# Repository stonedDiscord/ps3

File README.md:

# Playstation 3 schematics and board layout

This is a WIP KiCAD project for a custom PS3 motherboard.

I don't know if it's realistic but just maybe it's possible to use a newer CELL and RSX together with the PS2 EE/GS chips, since after all it's just simple PCI between them.

Shoutout to the PS3 dev wiki, it's been incredible helpful so far:
https://www.psdevwiki.com/ps3/Motherboard_Components

If you have high quality stripped board scans, I would appreciate a PR or an E-Mail with them.

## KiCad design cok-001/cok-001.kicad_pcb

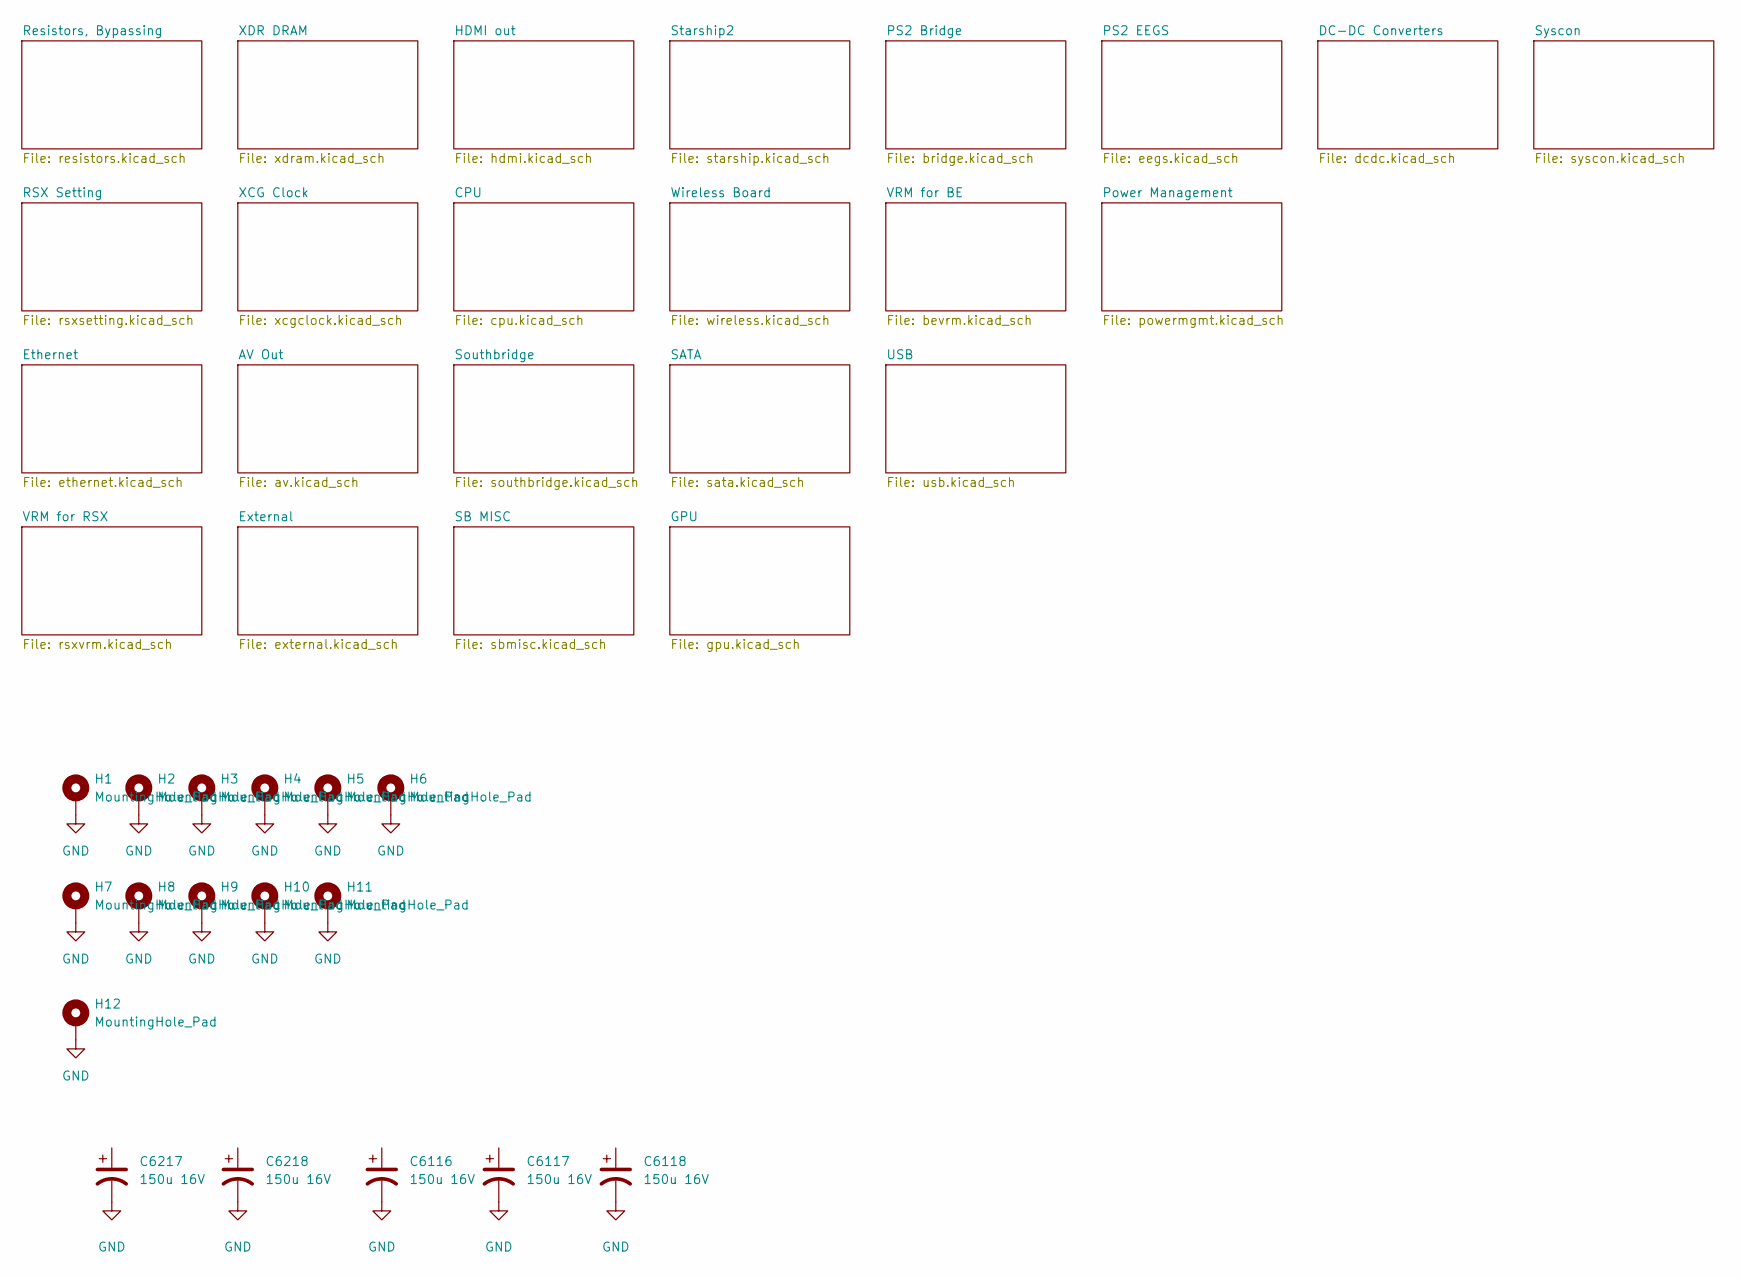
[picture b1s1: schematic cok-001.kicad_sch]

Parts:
C6116, C6117, C6118, C6217, C6218: 150u 16V; CP_Elec_8x6.9
H1, H2, H3, H4, H5, H6, H7, H8, H9, H10, H11: MountingHole_Pad; MountingHole_4.3mm_M4_Pad_Via
H12: MountingHole_Pad; MountingHole_4.3x6.2mm_M4_Pad_Via

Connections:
GND: C6116.2, C6117.2, C6118.2, C6217.2, C6218.2, H1.1 (1_1), H2.1 (1_1), H3.1 (1_1), H4.1 (1_1), H5.1 (1_1), H6.1 (1_1), H7.1 (1_1), H8.1 (1_1), H9.1 (1_1), H10.1 (1_1), H11.1 (1_1), H12.1 (1_1); also elsewhere on the board

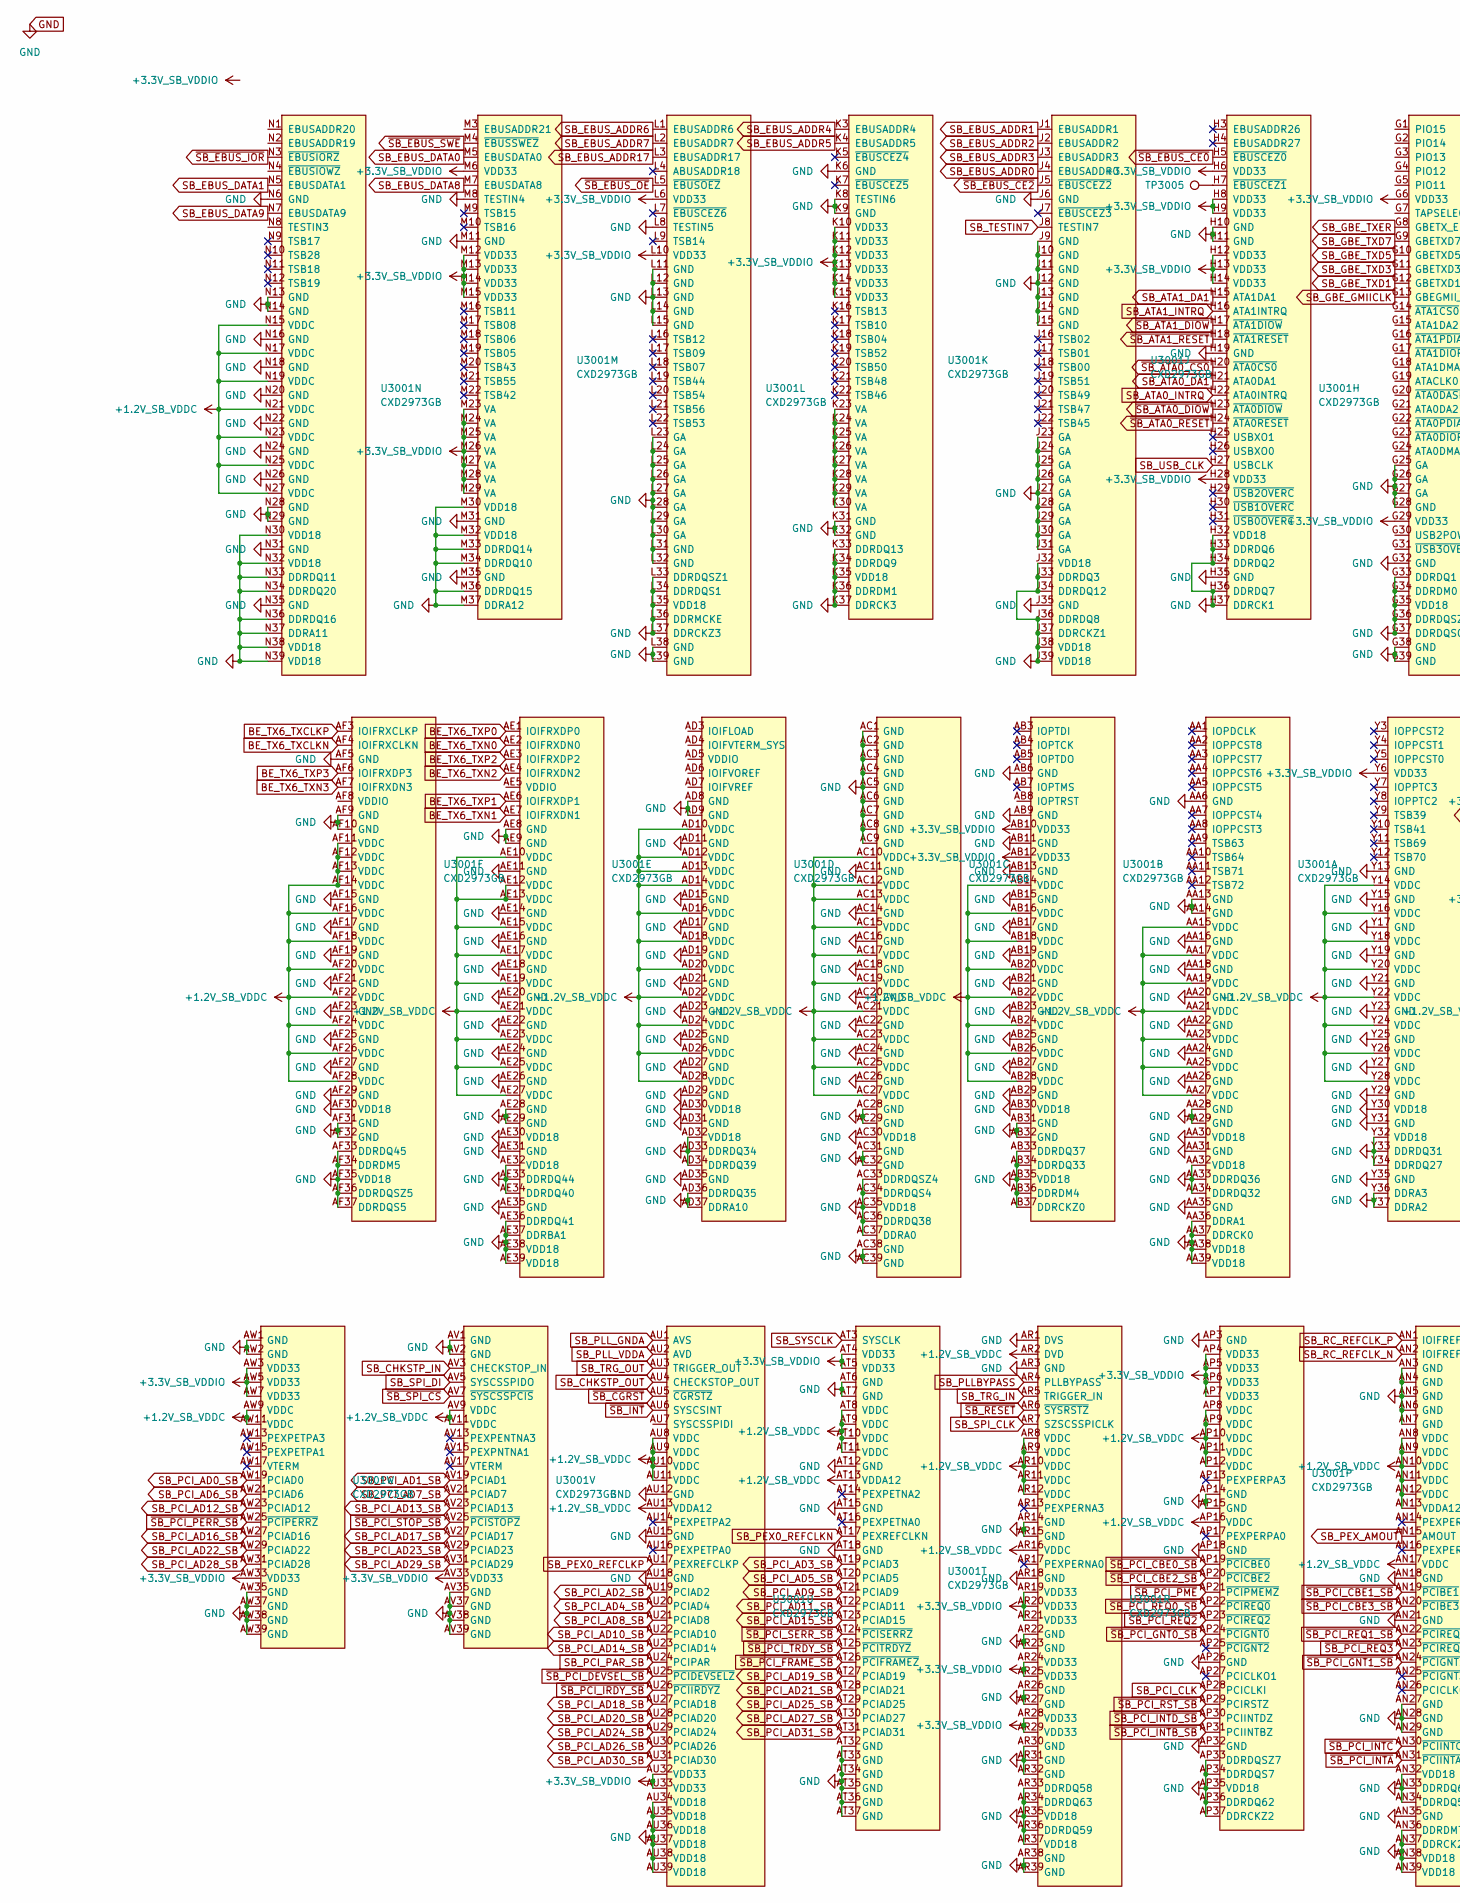
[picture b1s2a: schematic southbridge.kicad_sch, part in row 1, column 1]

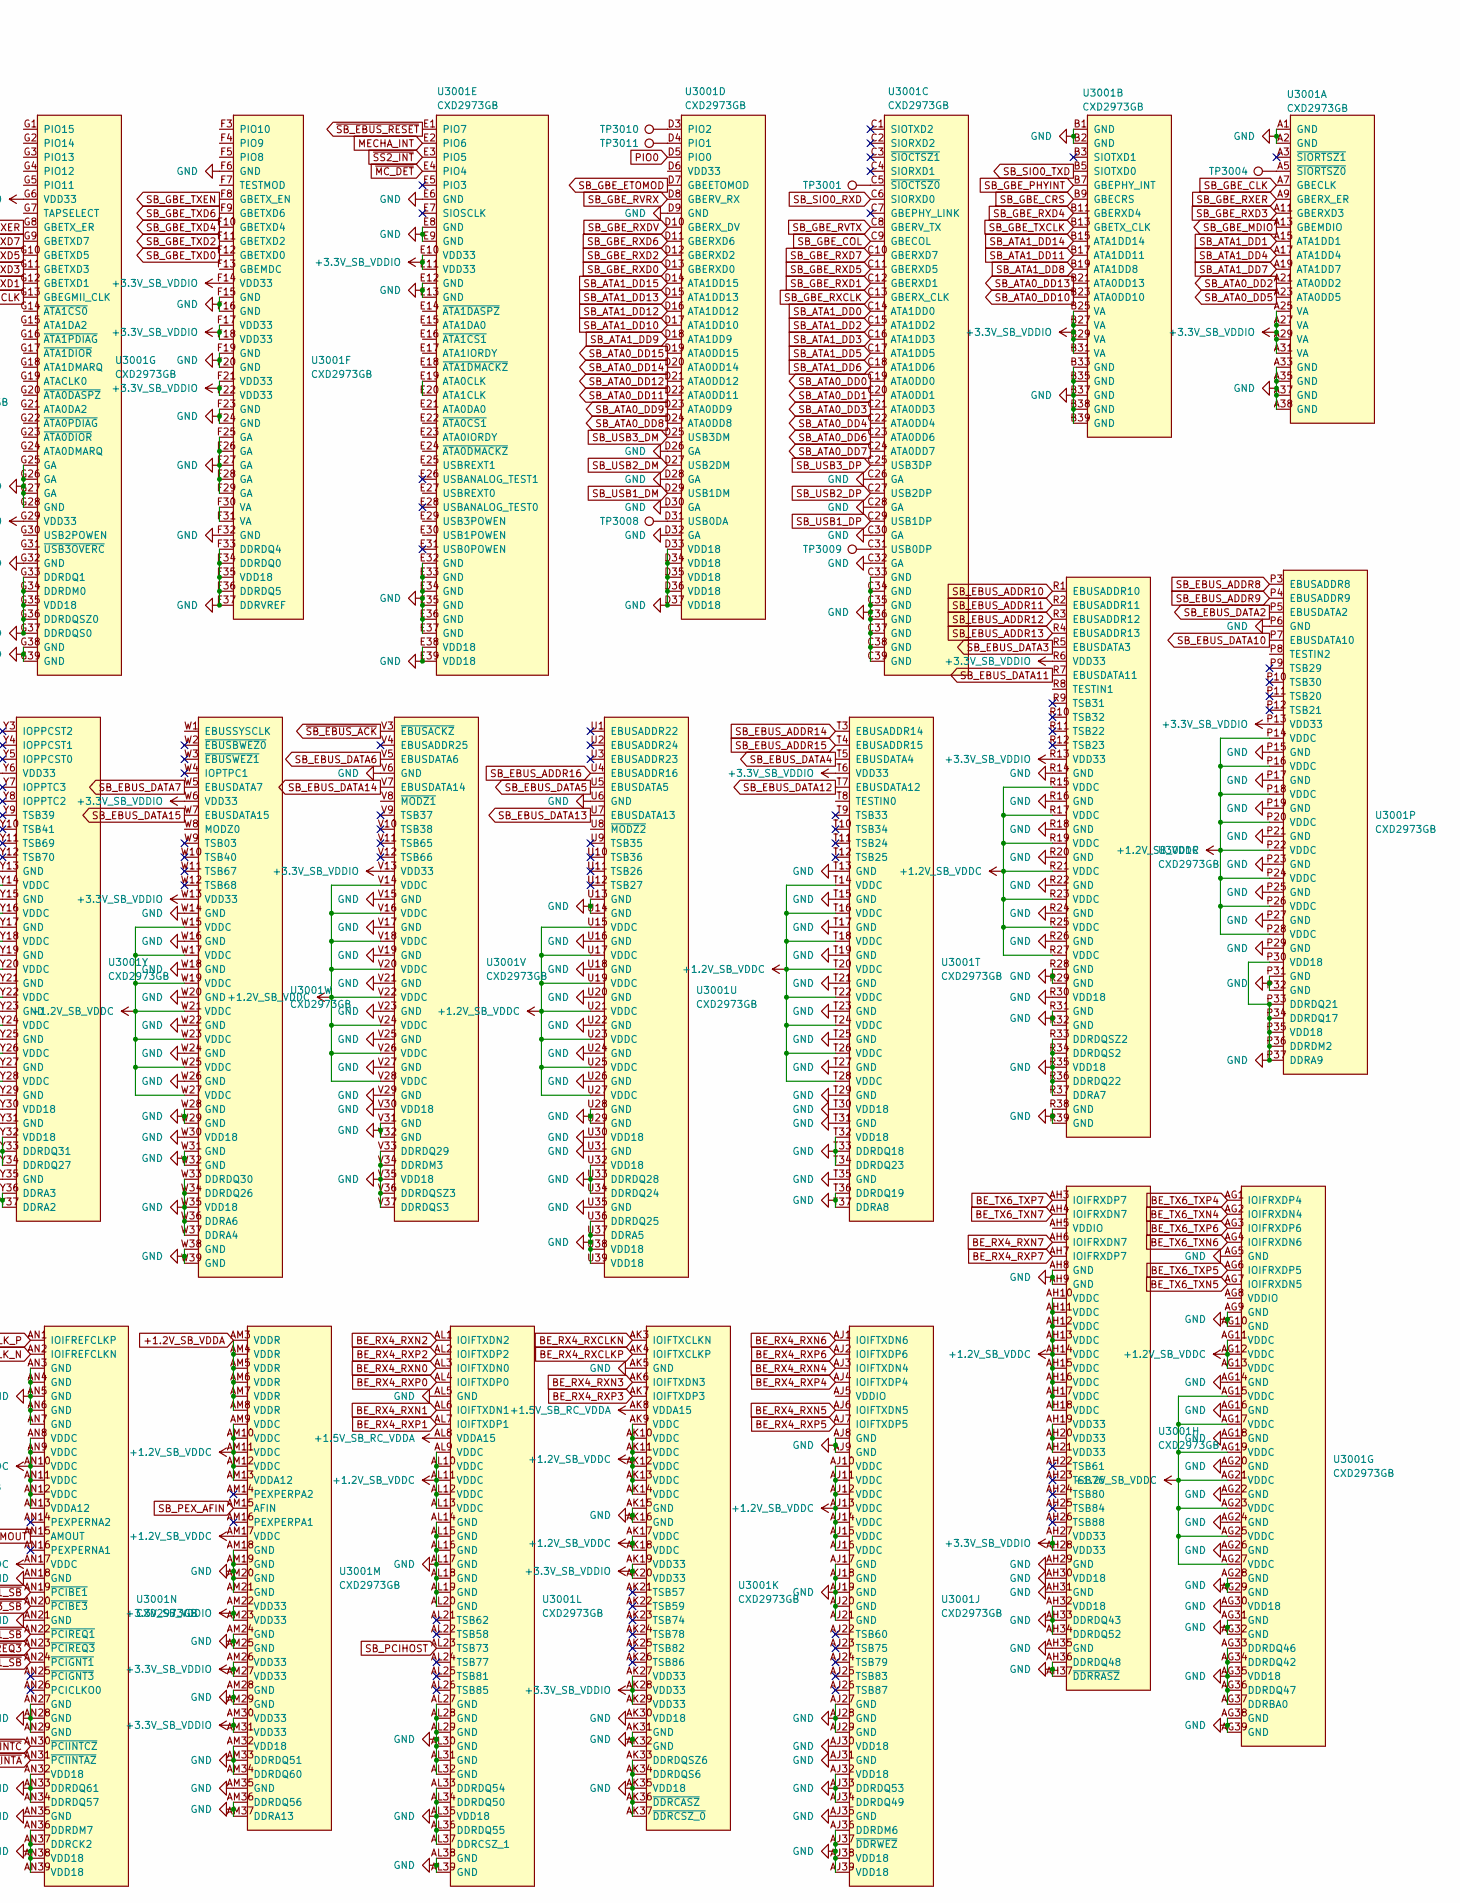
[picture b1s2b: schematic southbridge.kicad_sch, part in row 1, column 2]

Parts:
TP3001, TP3004, TP3005, TP3008, TP3009, TP3010, TP3011: TestPoint; TestPoint_Pad_1.0x1.0mm
U3001: CXD2973GB; SouthBridge

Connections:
+1.2V_SB_VDDA: U3001.AM3 (VDDR), U3001.AM4 (VDDR), U3001.AM5 (VDDR), U3001.AM6 (VDDR), U3001.AM7 (VDDR), U3001.AM8 (VDDR); also elsewhere on the board
+1.2V_SB_VDDC: U3001.AA15 (VDDC), U3001.AA17 (VDDC), U3001.AA19 (VDDC), U3001.AA21 (VDDC), U3001.AA23 (VDDC), U3001.AA25 (VDDC), U3001.AA27 (VDDC), U3001.AB14 (VDDC), U3001.AB16 (VDDC), U3001.AB18 (VDDC), U3001.AB20 (VDDC), U3001.AB22 (VDDC), U3001.AB24 (VDDC), U3001.AB26 (VDDC), U3001.AB28 (VDDC), U3001.AC10 (VDDC), U3001.AC12 (VDDC), U3001.AC13 (VDDC), U3001.AC15 (VDDC), U3001.AC17 (VDDC), U3001.AC19 (VDDC), U3001.AC21 (VDDC), U3001.AC23 (VDDC), U3001.AC25 (VDDC), U3001.AC27 (VDDC), U3001.AD10 (VDDC), U3001.AD12 (VDDC), U3001.AD13 (VDDC), U3001.AD14 (VDDC), U3001.AD16 (VDDC), U3001.AD18 (VDDC), U3001.AD20 (VDDC), U3001.AD22 (VDDC), U3001.AD24 (VDDC), U3001.AD26 (VDDC), U3001.AD28 (VDDC), U3001.AE10 (VDDC), U3001.AE12 (VDDC), U3001.AE13 (VDDC), U3001.AE15 (VDDC), U3001.AE17 (VDDC), U3001.AE19 (VDDC), U3001.AE21 (VDDC), U3001.AE23 (VDDC), U3001.AE25 (VDDC), U3001.AE27 (VDDC), U3001.AF11 (VDDC), U3001.AF12 (VDDC), U3001.AF13 (VDDC), U3001.AF14 (VDDC), U3001.AF16 (VDDC), U3001.AF18 (VDDC), U3001.AF20 (VDDC), U3001.AF22 (VDDC), U3001.AF24 (VDDC), U3001.AF26 (VDDC), U3001.AF28 (VDDC), U3001.AG11 (VDDC), U3001.AG12 (VDDC), U3001.AG13 (VDDC), U3001.AG15 (VDDC), U3001.AG17 (VDDC), U3001.AG19 (VDDC), U3001.AG21 (VDDC), U3001.AG23 (VDDC), U3001.AG25 (VDDC), U3001.AG27 (VDDC), U3001.AH10 (VDDC), U3001.AH11 (VDDC), U3001.AH12 (VDDC), U3001.AH13 (VDDC), U3001.AH14 (VDDC), U3001.AH15 (VDDC), U3001.AH16 (VDDC), U3001.AH17 (VDDC), U3001.AH18 (VDDC), U3001.AJ10 (VDDC), U3001.AJ11 (VDDC), U3001.AJ12 (VDDC), U3001.AJ13 (VDDC), U3001.AJ14 (VDDC), U3001.AJ15 (VDDC), U3001.AJ16 (VDDC), U3001.AK9 (VDDC), U3001.AK10 (VDDC), U3001.AK11 (VDDC), U3001.AK12 (VDDC), U3001.AK13 (VDDC), U3001.AK14 (VDDC), U3001.AK17 (VDDC), U3001.AK18 (VDDC), U3001.AL9 (VDDC), U3001.AL10 (VDDC), U3001.AL11 (VDDC), U3001.AL12 (VDDC), U3001.AL13 (VDDC), U3001.AM9 (VDDC), U3001.AM10 (VDDC), U3001.AM11 (VDDC), U3001.AM12 (VDDC), U3001.AM13 (VDDA12), U3001.AM17 (VDDC), U3001.AN8 (VDDC), U3001.AN9 (VDDC), U3001.AN10 (VDDC), U3001.AN11 (VDDC), U3001.AN12 (VDDC), U3001.AN13 (VDDA12), U3001.AN17 (VDDC), U3001.AP8 (VDDC), U3001.AP9 (VDDC), U3001.AP10 (VDDC), U3001.AP11 (VDDC), U3001.AP12 (VDDC), U3001.AP16 (VDDC), U3001.AR2 (DVD), U3001.AR8 (VDDC), U3001.AR9 (VDDC), U3001.AR10 (VDDC), U3001.AR11 (VDDC), U3001.AR12 (VDDC), U3001.AR16 (VDDC), U3001.AT8 (VDDC), U3001.AT9 (VDDC), U3001.AT10 (VDDC), U3001.AT11 (VDDC), U3001.AT13 (VDDA12), U3001.AU8 (VDDC), U3001.AU9 (VDDC), U3001.AU10 (VDDC), U3001.AU11 (VDDC), U3001.AU13 (VDDA12), U3001.AV9 (VDDC), U3001.AV11 (VDDC), U3001.AW9 (VDDC), U3001.AW11 (VDDC), U3001.N15 (VDDC), U3001.N17 (VDDC), U3001.N19 (VDDC), U3001.N21 (VDDC), U3001.N23 (VDDC), U3001.N25 (VDDC), U3001.N27 (VDDC), U3001.P14 (VDDC), U3001.P16 (VDDC), U3001.P18 (VDDC), U3001.P20 (VDDC), U3001.P22 (VDDC), U3001.P24 (VDDC), U3001.P26 (VDDC), U3001.P28 (VDDC), U3001.R15 (VDDC), U3001.R17 (VDDC), U3001.R19 (VDDC), U3001.R21 (VDDC), U3001.R23 (VDDC), U3001.R25 (VDDC), U3001.R27 (VDDC), U3001.T14 (VDDC), U3001.T16 (VDDC), U3001.T18 (VDDC), U3001.T20 (VDDC), U3001.T22 (VDDC), U3001.T24 (VDDC), U3001.T26 (VDDC), U3001.T28 (VDDC), U3001.U15 (VDDC), U3001.U17 (VDDC), U3001.U19 (VDDC), U3001.U21 (VDDC), U3001.U23 (VDDC), U3001.U25 (VDDC), U3001.U27 (VDDC), U3001.V14 (VDDC), U3001.V16 (VDDC), U3001.V18 (VDDC), U3001.V20 (VDDC), U3001.V22 (VDDC), U3001.V24 (VDDC), U3001.V26 (VDDC), U3001.V28 (VDDC), U3001.W15 (VDDC), U3001.W17 (VDDC), U3001.W19 (VDDC), U3001.W21 (VDDC), U3001.W23 (VDDC), U3001.W25 (VDDC), U3001.W27 (VDDC), U3001.Y14 (VDDC), U3001.Y16 (VDDC), U3001.Y18 (VDDC), U3001.Y20 (VDDC), U3001.Y22 (VDDC), U3001.Y24 (VDDC), U3001.Y26 (VDDC), U3001.Y28 (VDDC); also elsewhere on the board
+1.5V_SB_RC_VDDA: U3001.AK8 (VDDA15), U3001.AL8 (VDDA15)
+3.3V_SB_VDDIO: U3001.A25 (VA), U3001.A27 (VA), U3001.A29 (VA), U3001.A31 (VA), U3001.AB10 (VDD33), U3001.AB12 (VDD33), U3001.AH27 (VDD33), U3001.AH28 (VDD33), U3001.AK19 (VDD33), U3001.AK20 (VDD33), U3001.AK27 (VDD33), U3001.AK28 (VDD33), U3001.AK29 (VDD33), U3001.AM22 (VDD33), U3001.AM23 (VDD33), U3001.AM26 (VDD33), U3001.AM27 (VDD33), U3001.AM30 (VDD33), U3001.AM31 (VDD33), U3001.AP4 (VDD33), U3001.AP5 (VDD33), U3001.AP6 (VDD33), U3001.AP7 (VDD33), U3001.AR19 (VDD33), U3001.AR20 (VDD33), U3001.AR21 (VDD33), U3001.AR24 (VDD33), U3001.AR25 (VDD33), U3001.AR28 (VDD33), U3001.AR29 (VDD33), U3001.AT4 (VDD33), U3001.AT5 (VDD33), U3001.AU32 (VDD33), U3001.AU33 (VDD33), U3001.AV33 (VDD33), U3001.AW3 (VDD33), U3001.AW5 (VDD33), U3001.AW7 (VDD33), U3001.AW33 (VDD33), U3001.B25 (VA), U3001.B27 (VA), U3001.B29 (VA), U3001.B31 (VA), U3001.E10 (VDD33), U3001.E11 (VDD33), U3001.F14 (VDD33), U3001.F17 (VDD33), U3001.F18 (VDD33), U3001.F21 (VDD33), U3001.F22 (VDD33), U3001.G6 (VDD33), U3001.G29 (VDD33), U3001.H6 (VDD33), U3001.H8 (VDD33), U3001.H9 (VDD33), U3001.H12 (VDD33), U3001.H13 (VDD33), U3001.H14 (VDD33), U3001.H28 (VDD33), U3001.K10 (VDD33), U3001.K11 (VDD33), U3001.K12 (VDD33), U3001.K13 (VDD33), U3001.K14 (VDD33), U3001.K15 (VDD33), U3001.L6 (VDD33), U3001.L10 (VDD33), U3001.M6 (VDD33), U3001.M12 (VDD33), U3001.M13 (VDD33), U3001.M14 (VDD33), U3001.M15 (VDD33), U3001.M23 (VA), U3001.M24 (VA), U3001.M25 (VA), U3001.M26 (VA), U3001.M27 (VA), U3001.M28 (VA), U3001.M29 (VA), U3001.P13 (VDD33), U3001.R6 (VDD33), U3001.R13 (VDD33), U3001.T6 (VDD33), U3001.V13 (VDD33), U3001.W6 (VDD33), U3001.W13 (VDD33), U3001.Y6 (VDD33); also elsewhere on the board
BE_RX4_RXCLKN: U3001.AK3 (IOIFTXCLKN); also elsewhere on the board
BE_RX4_RXCLKP: U3001.AK4 (IOIFTXCLKP); also elsewhere on the board
BE_RX4_RXN0: U3001.AL3 (IOIFTXDN0); also elsewhere on the board
BE_RX4_RXN1: U3001.AL6 (IOIFTXDN1); also elsewhere on the board
BE_RX4_RXN2: U3001.AL1 (IOIFTXDN2); also elsewhere on the board
BE_RX4_RXN3: U3001.AK6 (IOIFTXDN3); also elsewhere on the board
BE_RX4_RXN4: U3001.AJ3 (IOIFTXDN4); also elsewhere on the board
BE_RX4_RXN5: U3001.AJ6 (IOIFTXDN5); also elsewhere on the board
BE_RX4_RXN6: U3001.AJ1 (IOIFTXDN6); also elsewhere on the board
BE_RX4_RXN7: U3001.AH6 (IOIFRXDN7); also elsewhere on the board
BE_RX4_RXP0: U3001.AL4 (IOIFTXDP0); also elsewhere on the board
BE_RX4_RXP1: U3001.AL7 (IOIFTXDP1); also elsewhere on the board
BE_RX4_RXP2: U3001.AL2 (IOIFTXDP2); also elsewhere on the board
BE_RX4_RXP3: U3001.AK7 (IOIFTXDP3); also elsewhere on the board
BE_RX4_RXP4: U3001.AJ4 (IOIFTXDP4); also elsewhere on the board
BE_RX4_RXP5: U3001.AJ7 (IOIFTXDP5); also elsewhere on the board
BE_RX4_RXP6: U3001.AJ2 (IOIFTXDP6); also elsewhere on the board
BE_RX4_RXP7: U3001.AH7 (IOIFRXDP7); also elsewhere on the board
BE_TX6_TXCLKN: U3001.AF4 (IOIFRXCLKN); also elsewhere on the board
BE_TX6_TXCLKP: U3001.AF3 (IOIFRXCLKP); also elsewhere on the board
BE_TX6_TXN0: U3001.AE2 (IOIFRXDN0); also elsewhere on the board
BE_TX6_TXN1: U3001.AE7 (IOIFRXDN1); also elsewhere on the board
BE_TX6_TXN2: U3001.AE4 (IOIFRXDN2); also elsewhere on the board
BE_TX6_TXN3: U3001.AF7 (IOIFRXDN3); also elsewhere on the board
BE_TX6_TXN4: U3001.AG2 (IOIFRXDN4); also elsewhere on the board
BE_TX6_TXN5: U3001.AG7 (IOIFRXDN5); also elsewhere on the board
BE_TX6_TXN6: U3001.AG4 (IOIFRXDN6); also elsewhere on the board
BE_TX6_TXN7: U3001.AH4 (IOIFRXDN7); also elsewhere on the board
BE_TX6_TXP0: U3001.AE1 (IOIFRXDP0); also elsewhere on the board
BE_TX6_TXP1: U3001.AE6 (IOIFRXDP1); also elsewhere on the board
BE_TX6_TXP2: U3001.AE3 (IOIFRXDP2); also elsewhere on the board
BE_TX6_TXP3: U3001.AF6 (IOIFRXDP3); also elsewhere on the board
BE_TX6_TXP4: U3001.AG1 (IOIFRXDP4); also elsewhere on the board
BE_TX6_TXP5: U3001.AG6 (IOIFRXDP5); also elsewhere on the board
BE_TX6_TXP6: U3001.AG3 (IOIFRXDP6); also elsewhere on the board
BE_TX6_TXP7: U3001.AH3 (IOIFRXDP7); also elsewhere on the board
GND: U3001.A1 (GND), U3001.A2 (GND), U3001.A33 (GND), U3001.A35 (GND), U3001.A37 (GND), U3001.A38 (GND), U3001.AA6 (GND), U3001.AA13 (GND), U3001.AA14 (GND), U3001.AA16 (GND), U3001.AA18 (GND), U3001.AA20 (GND), U3001.AA22 (GND), U3001.AA24 (GND), U3001.AA26 (GND), U3001.AA28 (GND), U3001.AA29 (GND), U3001.AA30 (VDD18), U3001.AA31 (GND), U3001.AA32 (VDD18), U3001.AA33 (DDRDQ36), U3001.AA34 (DDRDQ32), U3001.AA35 (GND), U3001.AA36 (DDRA1), U3001.AA37 (DDRCK0), U3001.AA38 (VDD18), U3001.AA39 (VDD18), U3001.AB6 (GND), U3001.AB9 (GND), U3001.AB11 (GND), U3001.AB13 (GND), U3001.AB15 (GND), U3001.AB17 (GND), U3001.AB19 (GND), U3001.AB21 (GND), U3001.AB23 (GND), U3001.AB25 (GND), U3001.AB27 (GND), U3001.AB29 (GND), U3001.AB30 (VDD18), U3001.AB31 (GND), U3001.AB32 (GND), U3001.AB33 (DDRDQ37), U3001.AB34 (DDRDQ33), U3001.AB35 (VDD18), U3001.AB36 (DDRDM4), U3001.AB37 (DDRCKZ0), U3001.AC1 (GND), U3001.AC2 (GND), U3001.AC3 (GND), U3001.AC4 (GND), U3001.AC5 (GND), U3001.AC6 (GND), U3001.AC7 (GND), U3001.AC8 (GND), U3001.AC9 (GND), U3001.AC11 (GND), U3001.AC14 (GND), U3001.AC16 (GND), U3001.AC18 (GND), U3001.AC20 (GND), U3001.AC22 (GND), U3001.AC24 (GND), U3001.AC26 (GND), U3001.AC28 (GND), U3001.AC29 (GND), U3001.AC30 (VDD18), U3001.AC31 (GND), U3001.AC32 (GND), U3001.AC33 (DDRDQSZ4), U3001.AC34 (DDRDQS4), U3001.AC35 (VDD18), U3001.AC36 (DDRDQ38), U3001.AC37 (DDRA0), U3001.AC38 (GND), U3001.AC39 (GND), U3001.AD8 (GND), U3001.AD9 (GND), U3001.AD11 (GND), U3001.AD15 (GND), U3001.AD17 (GND), U3001.AD19 (GND), U3001.AD21 (GND), U3001.AD23 (GND), U3001.AD25 (GND), U3001.AD27 (GND), U3001.AD29 (GND), U3001.AD30 (VDD18), U3001.AD31 (GND), U3001.AD32 (VDD18), U3001.AD33 (DDRDQ34), U3001.AD34 (DDRDQ39), U3001.AD35 (GND), U3001.AD36 (DDRDQ35), U3001.AD37 (DDRA10), U3001.AE8 (GND), U3001.AE9 (GND), U3001.AE11 (GND), U3001.AE14 (GND), U3001.AE16 (GND), U3001.AE18 (GND), U3001.AE20 (GND), U3001.AE22 (GND), U3001.AE24 (GND), U3001.AE26 (GND), U3001.AE28 (GND), U3001.AE29 (GND), U3001.AE30 (VDD18), U3001.AE31 (GND), U3001.AE32 (VDD18), U3001.AE33 (DDRDQ44), U3001.AE34 (DDRDQ40), U3001.AE35 (GND), U3001.AE36 (DDRDQ41), U3001.AE37 (DDRBA1), U3001.AE38 (VDD18), U3001.AE39 (VDD18), U3001.AF5 (GND), U3001.AF9 (GND), U3001.AF10 (GND), U3001.AF15 (GND), U3001.AF17 (GND), U3001.AF19 (GND), U3001.AF21 (GND), U3001.AF23 (GND), U3001.AF25 (GND), U3001.AF27 (GND), U3001.AF29 (GND), U3001.AF30 (VDD18), U3001.AF31 (GND), U3001.AF32 (GND), U3001.AF33 (DDRDQ45), U3001.AF34 (DDRDM5), U3001.AF35 (VDD18), U3001.AF36 (DDRDQSZ5), U3001.AF37 (DDRDQS5), U3001.AG5 (GND), U3001.AG9 (GND), U3001.AG10 (GND), U3001.AG14 (GND), U3001.AG16 (GND), U3001.AG18 (GND), U3001.AG20 (GND), U3001.AG22 (GND), U3001.AG24 (GND), U3001.AG26 (GND), U3001.AG28 (GND), U3001.AG29 (GND), U3001.AG30 (VDD18), U3001.AG31 (GND), U3001.AG32 (GND), U3001.AG33 (DDRDQ46), U3001.AG34 (DDRDQ42), U3001.AG35 (VDD18), U3001.AG36 (DDRDQ47), U3001.AG37 (DDRBA0), U3001.AG38 (GND), U3001.AG39 (GND), U3001.AH8 (GND), U3001.AH9 (GND), U3001.AH29 (GND), U3001.AH30 (VDD18), U3001.AH31 (GND), U3001.AH32 (VDD18), U3001.AH33 (DDRDQ43), U3001.AH34 (DDRDQ52), U3001.AH35 (GND), U3001.AH36 (DDRDQ48), U3001.AH37 (~DDRRASZ), U3001.AJ8 (GND), U3001.AJ9 (GND), U3001.AJ17 (GND), U3001.AJ18 (GND), U3001.AJ19 (GND), U3001.AJ20 (GND), U3001.AJ21 (GND), U3001.AJ27 (GND), U3001.AJ28 (GND), U3001.AJ29 (GND), U3001.AJ30 (VDD18), U3001.AJ31 (GND), U3001.AJ32 (VDD18), U3001.AJ33 (DDRDQ53), U3001.AJ34 (DDRDQ49), U3001.AJ35 (GND), U3001.AJ36 (DDRDM6), U3001.AJ37 (~DDRWEZ), U3001.AJ38 (VDD18), U3001.AJ39 (VDD18), U3001.AK5 (GND), U3001.AK15 (GND), U3001.AK16 (GND), U3001.AK30 (VDD18), U3001.AK31 (GND), U3001.AK32 (GND), U3001.AK33 (DDRDQSZ6), U3001.AK34 (DDRDQS6), U3001.AK35 (VDD18), U3001.AK36 (~DDRCASZ), U3001.AK37 (~DDRCSZ_0), U3001.AL5 (GND), U3001.AL14 (GND), U3001.AL15 (GND), U3001.AL16 (GND), U3001.AL17 (GND), U3001.AL18 (GND), U3001.AL19 (GND), U3001.AL20 (GND), U3001.AL27 (GND), U3001.AL28 (GND), U3001.AL29 (GND), U3001.AL30 (GND), U3001.AL31 (GND), U3001.AL32 (GND), U3001.AL33 (DDRDQ54), U3001.AL34 (DDRDQ50), U3001.AL35 (VDD18), U3001.AL36 (DDRDQ55), U3001.AL37 (DDRCSZ_1), U3001.AL38 (GND), U3001.AL39 (GND), U3001.AM18 (GND), U3001.AM19 (GND), U3001.AM20 (GND), U3001.AM21 (GND), U3001.AM24 (GND), U3001.AM25 (GND), U3001.AM28 (GND), U3001.AM29 (GND), U3001.AM32 (VDD18), U3001.AM33 (DDRDQ51), U3001.AM34 (DDRDQ60), U3001.AM35 (GND), U3001.AM36 (DDRDQ56), U3001.AM37 (DDRA13), U3001.AN3 (GND), U3001.AN4 (GND), U3001.AN5 (GND), U3001.AN6 (GND), U3001.AN7 (GND), U3001.AN18 (GND), U3001.AN21 (GND), U3001.AN27 (GND), U3001.AN28 (GND), U3001.AN29 (GND), U3001.AN32 (VDD18), U3001.AN33 (DDRDQ61), U3001.AN34 (DDRDQ57), U3001.AN35 (GND), U3001.AN36 (DDRDM7), U3001.AN37 (DDRCK2), U3001.AN38 (VDD18), U3001.AN39 (VDD18), U3001.AP3 (GND), U3001.AP14 (GND), U3001.AP15 (GND), U3001.AP18 (GND), U3001.AP26 (GND), U3001.AP32 (GND), U3001.AP33 (DDRDQSZ7), U3001.AP34 (DDRDQS7), U3001.AP35 (VDD18), U3001.AP36 (DDRDQ62), U3001.AP37 (DDRCKZ2), U3001.AR1 (DVS), U3001.AR3 (GND), U3001.AR14 (GND), U3001.AR15 (GND), U3001.AR18 (GND), U3001.AR22 (GND), U3001.AR23 (GND), U3001.AR26 (GND), U3001.AR27 (GND), U3001.AR30 (GND), U3001.AR31 (GND), U3001.AR32 (GND), U3001.AR33 (DDRDQ58), U3001.AR34 (DDRDQ63), U3001.AR35 (VDD18), U3001.AR36 (DDRDQ59), U3001.AR37 (VDD18), U3001.AR38 (GND), U3001.AR39 (GND), U3001.AT6 (GND), U3001.AT7 (GND), U3001.AT12 (GND), U3001.AT15 (GND), U3001.AT18 (GND), U3001.AT32 (GND), U3001.AT33 (GND), U3001.AT34 (GND), U3001.AT35 (GND), U3001.AT36 (GND), U3001.AT37 (GND), U3001.AU12 (GND), U3001.AU15 (GND), U3001.AU18 (GND), U3001.AU34 (VDD18), U3001.AU35 (VDD18), U3001.AU36 (VDD18), U3001.AU37 (VDD18), U3001.AU38 (VDD18), U3001.AU39 (VDD18), U3001.AV1 (GND), U3001.AV2 (GND), U3001.AV35 (GND), U3001.AV37 (GND), U3001.AV38 (GND), U3001.AV39 (GND), U3001.AW1 (GND), U3001.AW2 (GND), U3001.AW35 (GND), U3001.AW37 (GND), U3001.AW38 (GND), U3001.AW39 (GND), U3001.B1 (GND), U3001.B2 (GND), U3001.B33 (GND), U3001.B35 (GND), U3001.B37 (GND), U3001.B38 (GND), U3001.B39 (GND), U3001.C26 (GA), U3001.C28 (GA), U3001.C30 (GA), U3001.C32 (GA), U3001.C33 (GND), U3001.C34 (GND), U3001.C35 (GND), U3001.C36 (GND), U3001.C37 (GND), U3001.C38 (GND), U3001.C39 (GND), U3001.D9 (GND), U3001.D26 (GA), U3001.D28 (GA), U3001.D30 (GA), U3001.D32 (GA), U3001.D33 (VDD18), U3001.D34 (VDD18), U3001.D35 (VDD18), U3001.D36 (VDD18), U3001.D37 (VDD18), U3001.E6 (GND), U3001.E8 (GND), U3001.E9 (GND), U3001.E12 (GND), U3001.E13 (GND), U3001.E32 (GND), U3001.E33 (GND), U3001.E34 (GND), U3001.E35 (GND), U3001.E36 (GND), U3001.E37 (GND), U3001.E38 (VDD18), U3001.E39 (VDD18), U3001.F6 (GND), U3001.F15 (GND), U3001.F16 (GND), U3001.F19 (GND), U3001.F20 (GND), U3001.F23 (GND), U3001.F24 (GND), U3001.F25 (GA), U3001.F26 (GA), U3001.F27 (GA), U3001.F28 (GA), U3001.F29 (GA), U3001.F32 (GND), U3001.F33 (DDRDQ4), U3001.F34 (DDRDQ0), U3001.F35 (VDD18), U3001.F36 (DDRDQ5), U3001.F37 (DDRVREF), U3001.G25 (GA), U3001.G26 (GA), U3001.G27 (GA), U3001.G28 (GND), U3001.G32 (GND), U3001.G33 (DDRDQ1), U3001.G34 (DDRDM0), U3001.G35 (VDD18), U3001.G36 (DDRDQSZ0), U3001.G37 (DDRDQS0), U3001.G38 (GND), U3001.G39 (GND), U3001.H10 (GND), U3001.H11 (GND), U3001.H19 (GND), U3001.H32 (VDD18), U3001.H33 (DDRDQ6), U3001.H34 (DDRDQ2), U3001.H35 (GND), U3001.H36 (DDRDQ7), U3001.H37 (DDRCK1), U3001.J6 (GND), U3001.J9 (GND), U3001.J10 (GND), U3001.J11 (GND), U3001.J12 (GND), U3001.J13 (GND), U3001.J14 (GND), U3001.J15 (GND), U3001.J23 (GA), U3001.J24 (GA), U3001.J25 (GA), U3001.J26 (GA), U3001.J27 (GA), U3001.J28 (GA), U3001.J29 (GA), U3001.J30 (GA), U3001.J31 (GA), U3001.J32 (VDD18), U3001.J33 (DDRDQ3), U3001.J34 (DDRDQ12), U3001.J35 (GND), U3001.J36 (DDRDQ8), U3001.J37 (DDRCKZ1), U3001.J38 (VDD18), U3001.J39 (VDD18), U3001.K6 (GND), U3001.K8 (TESTIN6), U3001.K9 (GND), U3001.K31 (GND), U3001.K32 (GND), U3001.K33 (DDRDQ13), U3001.K34 (DDRDQ9), U3001.K35 (VDD18), U3001.K36 (DDRDM1), U3001.K37 (DDRCK3), U3001.L8 (TESTIN5), U3001.L11 (GND), U3001.L12 (GND), U3001.L13 (GND), U3001.L14 (GND), U3001.L15 (GND), U3001.L23 (GA), U3001.L24 (GA), U3001.L25 (GA), U3001.L26 (GA), U3001.L27 (GA), U3001.L28 (GA), U3001.L29 (GA), U3001.L30 (GA), U3001.L31 (GND), U3001.L32 (GND), U3001.L33 (DDRDQSZ1), U3001.L34 (DDRDQS1), U3001.L35 (VDD18), U3001.L36 (DDRMCKE), U3001.L37 (DDRCKZ3), U3001.L38 (GND), U3001.L39 (GND), U3001.M8 (TESTIN4), U3001.M11 (GND), U3001.M30 (VDD18), U3001.M31 (GND), U3001.M32 (VDD18), U3001.M33 (DDRDQ14), U3001.M34 (DDRDQ10), U3001.M35 (GND), U3001.M36 (DDRDQ15), U3001.M37 (DDRA12), U3001.N6 (GND), U3001.N13 (GND), U3001.N14 (GND), U3001.N16 (GND), U3001.N18 (GND), U3001.N20 (GND), U3001.N22 (GND), U3001.N24 (GND), U3001.N26 (GND), U3001.N28 (GND), U3001.N29 (GND), U3001.N30 (VDD18), U3001.N31 (GND), U3001.N32 (VDD18), U3001.N33 (DDRDQ11), U3001.N34 (DDRDQ20), U3001.N35 (GND), U3001.N36 (DDRDQ16), U3001.N37 (DDRA11), U3001.N38 (VDD18), U3001.N39 (VDD18), U3001.P6 (GND), U3001.P15 (GND), U3001.P17 (GND), U3001.P19 (GND), U3001.P21 (GND), U3001.P23 (GND), U3001.P25 (GND), U3001.P27 (GND), U3001.P29 (GND), U3001.P30 (VDD18), U3001.P31 (GND), U3001.P32 (GND), U3001.P33 (DDRDQ21), U3001.P34 (DDRDQ17), U3001.P35 (VDD18), U3001.P36 (DDRDM2), U3001.P37 (DDRA9), U3001.R14 (GND), U3001.R16 (GND), U3001.R18 (GND), U3001.R20 (GND), U3001.R22 (GND), U3001.R24 (GND), U3001.R26 (GND), U3001.R28 (GND), U3001.R29 (GND), U3001.R30 (VDD18), U3001.R31 (GND), U3001.R32 (GND), U3001.R33 (DDRDQSZ2), U3001.R34 (DDRDQS2), U3001.R35 (VDD18), U3001.R36 (DDRDQ22), U3001.R37 (DDRA7), U3001.R38 (GND), U3001.R39 (GND), U3001.T13 (GND), U3001.T15 (GND), U3001.T17 (GND), U3001.T19 (GND), U3001.T21 (GND), U3001.T23 (GND), U3001.T25 (GND), U3001.T27 (GND), U3001.T29 (GND), U3001.T30 (VDD18), U3001.T31 (GND), U3001.T32 (VDD18), U3001.T33 (DDRDQ18), U3001.T34 (DDRDQ23)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; also elsewhere on the board
MECHA_INT: U3001.E2 (PIO6); also elsewhere on the board
unnamed: TP3004.1 (1_1), U3001.A5 (~SIORTSZ0)
unnamed: U3001.AH19 (VDD33), U3001.AH20 (VDD33), U3001.AH21 (VDD33)
unnamed: TP3009.1 (1_1), U3001.C31 (USB0DP)
unnamed: TP3001.1 (1_1), U3001.C5 (~SIOCTSZ0)
unnamed: TP3011.1 (1_1), U3001.D4 (PIO1)
unnamed: TP3010.1 (1_1), U3001.D3 (PIO2)
unnamed: TP3008.1 (1_1), U3001.D31 (USB0DA)
unnamed: U3001.E19 (ATA0CLK), U3001.E20 (ATA1CLK)
unnamed: U3001.F30 (VA), U3001.F31 (VA)
unnamed: TP3005.1 (1_1), U3001.H7 (~EBUSCEZ1)
unnamed: U3001.K23 (VA), U3001.K24 (VA), U3001.K25 (VA), U3001.K26 (VA), U3001.K27 (VA), U3001.K28 (VA), U3001.K29 (VA), U3001.K30 (VA)
PIO0: U3001.D5 (PIO0)
SB_ATA0_DA1: U3001.H21 (ATA0DA1); also elsewhere on the board
SB_ATA0_DD0: U3001.C19 (ATA0DD0); also elsewhere on the board
SB_ATA0_DD1: U3001.C20 (ATA0DD1); also elsewhere on the board
SB_ATA0_DD2: U3001.A21 (ATA0DD2); also elsewhere on the board
SB_ATA0_DD3: U3001.C21 (ATA0DD3); also elsewhere on the board
SB_ATA0_DD4: U3001.C22 (ATA0DD4); also elsewhere on the board
SB_ATA0_DD5: U3001.A23 (ATA0DD5); also elsewhere on the board
SB_ATA0_DD6: U3001.C23 (ATA0DD6); also elsewhere on the board
SB_ATA0_DD7: U3001.C24 (ATA0DD7); also elsewhere on the board
SB_ATA0_DD8: U3001.D24 (ATA0DD8); also elsewhere on the board
SB_ATA0_DD9: U3001.D23 (ATA0DD9); also elsewhere on the board
SB_ATA0_DD10: U3001.B23 (ATA0DD10); also elsewhere on the board
SB_ATA0_DD11: U3001.D22 (ATA0DD11); also elsewhere on the board
SB_ATA0_DD12: U3001.D21 (ATA0DD12); also elsewhere on the board
SB_ATA0_DD13: U3001.B21 (ATA0DD13); also elsewhere on the board
SB_ATA0_DD14: U3001.D20 (ATA0DD14); also elsewhere on the board
SB_ATA0_DD15: U3001.D19 (ATA0DD15); also elsewhere on the board
SB_ATA0_INTRQ: U3001.H22 (ATA0INTRQ); also elsewhere on the board
SB_ATA1_DA1: U3001.H15 (ATA1DA1); also elsewhere on the board
SB_ATA1_DD0: U3001.C14 (ATA1DD0); also elsewhere on the board
SB_ATA1_DD1: U3001.A15 (ATA1DD1); also elsewhere on the board
SB_ATA1_DD2: U3001.C15 (ATA1DD2); also elsewhere on the board
SB_ATA1_DD3: U3001.C16 (ATA1DD3); also elsewhere on the board
SB_ATA1_DD4: U3001.A17 (ATA1DD4); also elsewhere on the board
SB_ATA1_DD5: U3001.C17 (ATA1DD5); also elsewhere on the board
SB_ATA1_DD6: U3001.C18 (ATA1DD6); also elsewhere on the board
SB_ATA1_DD7: U3001.A19 (ATA1DD7); also elsewhere on the board
SB_ATA1_DD8: U3001.B19 (ATA1DD8); also elsewhere on the board
SB_ATA1_DD9: U3001.D18 (ATA1DD9); also elsewhere on the board
SB_ATA1_DD10: U3001.D17 (ATA1DD10); also elsewhere on the board
SB_ATA1_DD11: U3001.B17 (ATA1DD11); also elsewhere on the board
SB_ATA1_DD12: U3001.D16 (ATA1DD12); also elsewhere on the board
SB_ATA1_DD13: U3001.D15 (ATA1DD13); also elsewhere on the board
SB_ATA1_DD14: U3001.B15 (ATA1DD14); also elsewhere on the board
SB_ATA1_DD15: U3001.D14 (ATA1DD15); also elsewhere on the board
SB_ATA1_INTRQ: U3001.H16 (ATA1INTRQ); also elsewhere on the board
SB_CHKSTP_IN: U3001.AV3 (CHECKSTOP_IN); also elsewhere on the board
SB_CHKSTP_OUT: U3001.AU4 (CHECKSTOP_OUT); also elsewhere on the board
SB_EBUS_ADDR0: U3001.J4 (EBUSADDR0); also elsewhere on the board
SB_EBUS_ADDR1: U3001.J1 (EBUSADDR1); also elsewhere on the board
SB_EBUS_ADDR2: U3001.J2 (EBUSADDR2); also elsewhere on the board
SB_EBUS_ADDR3: U3001.J3 (EBUSADDR3); also elsewhere on the board
SB_EBUS_ADDR4: U3001.K3 (EBUSADDR4); also elsewhere on the board
SB_EBUS_ADDR5: U3001.K4 (EBUSADDR5); also elsewhere on the board
SB_EBUS_ADDR6: U3001.L1 (EBUSADDR6); also elsewhere on the board
SB_EBUS_ADDR7: U3001.L2 (EBUSADDR7); also elsewhere on the board
SB_EBUS_ADDR8: U3001.P3 (EBUSADDR8); also elsewhere on the board
SB_EBUS_ADDR9: U3001.P4 (EBUSADDR9); also elsewhere on the board
SB_EBUS_ADDR10: U3001.R1 (EBUSADDR10); also elsewhere on the board
SB_EBUS_ADDR11: U3001.R2 (EBUSADDR11); also elsewhere on the board
SB_EBUS_ADDR12: U3001.R3 (EBUSADDR12); also elsewhere on the board
SB_EBUS_ADDR13: U3001.R4 (EBUSADDR13); also elsewhere on the board
SB_EBUS_ADDR14: U3001.T3 (EBUSADDR14); also elsewhere on the board
SB_EBUS_ADDR15: U3001.T4 (EBUSADDR15); also elsewhere on the board
SB_EBUS_ADDR16: U3001.U4 (EBUSADDR16); also elsewhere on the board
SB_EBUS_ADDR17: U3001.L3 (EBUSADDR17); also elsewhere on the board
SB_EBUS_DATA0: U3001.M5 (EBUSDATA0); also elsewhere on the board
SB_EBUS_DATA1: U3001.N5 (EBUSDATA1); also elsewhere on the board
SB_EBUS_DATA2: U3001.P5 (EBUSDATA2); also elsewhere on the board
SB_EBUS_DATA3: U3001.R5 (EBUSDATA3); also elsewhere on the board
SB_EBUS_DATA4: U3001.T5 (EBUSDATA4); also elsewhere on the board
SB_EBUS_DATA5: U3001.U5 (EBUSDATA5); also elsewhere on the board
SB_EBUS_DATA6: U3001.V5 (EBUSDATA6); also elsewhere on the board
SB_EBUS_DATA7: U3001.W5 (EBUSDATA7); also elsewhere on the board
SB_EBUS_DATA8: U3001.M7 (EBUSDATA8); also elsewhere on the board
SB_EBUS_DATA9: U3001.N7 (EBUSDATA9); also elsewhere on the board
SB_EBUS_DATA10: U3001.P7 (EBUSDATA10); also elsewhere on the board
SB_EBUS_DATA11: U3001.R7 (EBUSDATA11); also elsewhere on the board
SB_EBUS_DATA12: U3001.T7 (EBUSDATA12); also elsewhere on the board
SB_EBUS_DATA13: U3001.U7 (EBUSDATA13); also elsewhere on the board
SB_EBUS_DATA14: U3001.V7 (EBUSDATA14); also elsewhere on the board
SB_EBUS_DATA15: U3001.W7 (EBUSDATA15); also elsewhere on the board
SB_GBE_CLK: U3001.A7 (GBECLK); also elsewhere on the board
SB_GBE_COL: U3001.C9 (GBECOL)
SB_GBE_CRS: U3001.B9 (GBECRS)
SB_GBE_ETOMOD: U3001.D7 (GBEETOMOD); also elsewhere on the board
SB_GBE_GMIICLK: U3001.G13 (GBEGMII_CLK); also elsewhere on the board
SB_GBE_MDIO: U3001.A13 (GBEMDIO)
SB_GBE_PHYINT: U3001.B7 (GBEPHY_INT)
SB_GBE_RVRX: U3001.D8 (GBERV_RX); also elsewhere on the board
SB_GBE_RVTX: U3001.C8 (GBERV_TX); also elsewhere on the board
SB_GBE_RXCLK: U3001.C13 (GBERX_CLK)
SB_GBE_RXD0: U3001.D13 (GBERXD0); also elsewhere on the board
SB_GBE_RXD1: U3001.C12 (GBERXD1); also elsewhere on the board
SB_GBE_RXD2: U3001.D12 (GBERXD2); also elsewhere on the board
SB_GBE_RXD3: U3001.A11 (GBERXD3); also elsewhere on the board
SB_GBE_RXD4: U3001.B11 (GBERXD4); also elsewhere on the board
SB_GBE_RXD5: U3001.C11 (GBERXD5); also elsewhere on the board
SB_GBE_RXD6: U3001.D11 (GBERXD6); also elsewhere on the board
SB_GBE_RXD7: U3001.C10 (GBERXD7); also elsewhere on the board
SB_GBE_RXDV: U3001.D10 (GBERX_DV)
SB_GBE_RXER: U3001.A9 (GBERX_ER)
SB_GBE_TXCLK: U3001.B13 (GBETX_CLK); also elsewhere on the board
SB_GBE_TXD0: U3001.F12 (GBETXD0); also elsewhere on the board
SB_GBE_TXD1: U3001.G12 (GBETXD1); also elsewhere on the board
SB_GBE_TXD2: U3001.F11 (GBETXD2); also elsewhere on the board
SB_GBE_TXD3: U3001.G11 (GBETXD3); also elsewhere on the board
SB_GBE_TXD4: U3001.F10 (GBETXD4); also elsewhere on the board
SB_GBE_TXD5: U3001.G10 (GBETXD5); also elsewhere on the board
SB_GBE_TXD6: U3001.F9 (GBETXD6); also elsewhere on the board
SB_GBE_TXD7: U3001.G9 (GBETXD7); also elsewhere on the board
SB_GBE_TXEN: U3001.F8 (GBETX_EN); also elsewhere on the board
SB_GBE_TXER: U3001.G8 (GBETX_ER); also elsewhere on the board
SB_PCIHOST: U3001.AL23 (TSB73); also elsewhere on the board
SB_PCI_AD0_SB: U3001.AW19 (PCIAD0); also elsewhere on the board
SB_PCI_AD1_SB: U3001.AV19 (PCIAD1); also elsewhere on the board
SB_PCI_AD2_SB: U3001.AU19 (PCIAD2); also elsewhere on the board
SB_PCI_AD3_SB: U3001.AT19 (PCIAD3); also elsewhere on the board
SB_PCI_AD4_SB: U3001.AU20 (PCIAD4); also elsewhere on the board
SB_PCI_AD5_SB: U3001.AT20 (PCIAD5); also elsewhere on the board
SB_PCI_AD6_SB: U3001.AW21 (PCIAD6); also elsewhere on the board
SB_PCI_AD7_SB: U3001.AV21 (PCIAD7); also elsewhere on the board
SB_PCI_AD8_SB: U3001.AU21 (PCIAD8); also elsewhere on the board
SB_PCI_AD9_SB: U3001.AT21 (PCIAD9); also elsewhere on the board
SB_PCI_AD10_SB: U3001.AU22 (PCIAD10); also elsewhere on the board
SB_PCI_AD11_SB: U3001.AT22 (PCIAD11); also elsewhere on the board
SB_PCI_AD12_SB: U3001.AW23 (PCIAD12); also elsewhere on the board
SB_PCI_AD13_SB: U3001.AV23 (PCIAD13); also elsewhere on the board
SB_PCI_AD14_SB: U3001.AU23 (PCIAD14); also elsewhere on the board
SB_PCI_AD15_SB: U3001.AT23 (PCIAD15); also elsewhere on the board
SB_PCI_AD16_SB: U3001.AW27 (PCIAD16)
SB_PCI_AD17_SB: U3001.AV27 (PCIAD17); also elsewhere on the board
SB_PCI_AD18_SB: U3001.AU27 (PCIAD18); also elsewhere on the board
SB_PCI_AD19_SB: U3001.AT27 (PCIAD19); also elsewhere on the board
SB_PCI_AD20_SB: U3001.AU28 (PCIAD20); also elsewhere on the board
SB_PCI_AD21_SB: U3001.AT28 (PCIAD21); also elsewhere on the board
SB_PCI_AD22_SB: U3001.AW29 (PCIAD22); also elsewhere on the board
SB_PCI_AD23_SB: U3001.AV29 (PCIAD23); also elsewhere on the board
SB_PCI_AD24_SB: U3001.AU29 (PCIAD24); also elsewhere on the board
SB_PCI_AD25_SB: U3001.AT29 (PCIAD25); also elsewhere on the board
SB_PCI_AD26_SB: U3001.AU30 (PCIAD26); also elsewhere on the board
SB_PCI_AD27_SB: U3001.AT30 (PCIAD27); also elsewhere on the board
SB_PCI_AD28_SB: U3001.AW31 (PCIAD28); also elsewhere on the board
SB_PCI_AD29_SB: U3001.AV31 (PCIAD29); also elsewhere on the board
SB_PCI_AD30_SB: U3001.AU31 (PCIAD30); also elsewhere on the board
SB_PCI_AD31_SB: U3001.AT31 (PCIAD31); also elsewhere on the board
SB_PCI_CLK: U3001.AP28 (PCICLKI); also elsewhere on the board
SB_PCI_PAR_SB: U3001.AU24 (PCIPAR); also elsewhere on the board
SB_PEX0_REFCLKN: U3001.AT17 (PEXREFCLKN); also elsewhere on the board
SB_PEX0_REFCLKP: U3001.AU17 (PEXREFCLKP); also elsewhere on the board
SB_PEX_AFIN: U3001.AM15 (AFIN); also elsewhere on the board
SB_PEX_AMOUT: U3001.AN15 (AMOUT); also elsewhere on the board
SB_PLLBYPASS: U3001.AR4 (PLLBYPASS); also elsewhere on the board
SB_PLL_GNDA: U3001.AU1 (AVS)
SB_PLL_VDDA: U3001.AU2 (AVD)
SB_RC_REFCLK_N: U3001.AN2 (IOIFREFCLKN)
SB_RC_REFCLK_P: U3001.AN1 (IOIFREFCLKP)
SB_SIO0_RXD: U3001.C6 (SIORXD0); also elsewhere on the board
SB_SIO0_TXD: U3001.B5 (SIOTXD0); also elsewhere on the board
SB_SPI_CLK: U3001.AR7 (SZSCSSPICLK); also elsewhere on the board
SB_SPI_DI: U3001.AV5 (SYSCSSPIDO)
SB_SYSCLK: U3001.AT3 (SYSCLK); also elsewhere on the board
SB_TESTIN7: U3001.J8 (TESTIN7); also elsewhere on the board
SB_TRG_IN: U3001.AR5 (TRIGGER_IN); also elsewhere on the board
SB_TRG_OUT: U3001.AU3 (TRIGGER_OUT); also elsewhere on the board
SB_USB1_DM: U3001.D29 (USB1DM); also elsewhere on the board
SB_USB1_DP: U3001.C29 (USB1DP); also elsewhere on the board
SB_USB2_DM: U3001.D27 (USB2DM)
SB_USB2_DP: U3001.C27 (USB2DP)
SB_USB3_DM: U3001.D25 (USB3DM)
SB_USB3_DP: U3001.C25 (USB3DP); also elsewhere on the board
SB_USB_CLK: U3001.H27 (USBCLK); also elsewhere on the board
~MC_DET: U3001.E4 (PIO4); also elsewhere on the board
~SB_ATA0_CS0: U3001.H20 (~ATA0CS0)
~SB_ATA0_DIOW: U3001.H23 (~ATA0DIOW)
~SB_ATA0_RESET: U3001.H24 (~ATA0RESET); also elsewhere on the board
~SB_ATA1_DIOW: U3001.H17 (~ATA1DIOW); also elsewhere on the board
~SB_ATA1_RESET: U3001.H18 (~ATA1RESET); also elsewhere on the board
~SB_CGRST: U3001.AU5 (~CGRSTZ)
~SB_EBUS_ACK: U3001.V3 (~EBUSACKZ); also elsewhere on the board
~SB_EBUS_CE0: U3001.H5 (~EBUSCEZ0); also elsewhere on the board
~SB_EBUS_CE2: U3001.J5 (~EBUSCEZ2); also elsewhere on the board
~SB_EBUS_IOR: U3001.N3 (~EBUSIORZ); also elsewhere on the board
~SB_EBUS_OE: U3001.L5 (~EBUSOEZ); also elsewhere on the board
~SB_EBUS_RESET: U3001.E1 (PIO7); also elsewhere on the board
~SB_EBUS_SWE: U3001.M4 (~EBUSSWEZ); also elsewhere on the board
~SB_INT: U3001.AU6 (SYSCSINT); also elsewhere on the board
~SB_PCI_CBE0_SB: U3001.AP19 (~PCICBE0); also elsewhere on the board
~SB_PCI_CBE1_SB: U3001.AN19 (~PCIBE1); also elsewhere on the board
~SB_PCI_CBE2_SB: U3001.AP20 (~PCICBE2); also elsewhere on the board
~SB_PCI_CBE3_SB: U3001.AN20 (~PCIBE3); also elsewhere on the board
~SB_PCI_DEVSEL_SB: U3001.AU25 (~PCIDEVSELZ); also elsewhere on the board
~SB_PCI_FRAME_SB: U3001.AT26 (~PCIFRAMEZ)
~SB_PCI_GNT0_SB: U3001.AP24 (~PCIGNT0)
~SB_PCI_GNT1_SB: U3001.AN24 (~PCIGNT1); also elsewhere on the board
~SB_PCI_INTA: U3001.AN31 (~PCIINTAZ); also elsewhere on the board
~SB_PCI_INTB_SB: U3001.AP31 (PCIINTBZ)
~SB_PCI_INTC: U3001.AN30 (~PCIINTCZ); also elsewhere on the board
~SB_PCI_INTD_SB: U3001.AP30 (PCIINTDZ)
~SB_PCI_IRDY_SB: U3001.AU26 (~PCIIRDYZ); also elsewhere on the board
~SB_PCI_PERR_SB: U3001.AW25 (~PCIPERRZ); also elsewhere on the board
~SB_PCI_PME: U3001.AP21 (~PCIPMEMZ); also elsewhere on the board
~SB_PCI_REQ0_SB: U3001.AP22 (~PCIREQ0)
~SB_PCI_REQ1_SB: U3001.AN22 (~PCIREQ1)
~SB_PCI_REQ2: U3001.AP23 (~PCIREQ2)
~SB_PCI_REQ3: U3001.AN23 (~PCIREQ3)
~SB_PCI_RST_SB: U3001.AP29 (PCIRSTZ); also elsewhere on the board
~SB_PCI_SERR_SB: U3001.AT24 (~PCISERRZ); also elsewhere on the board
~SB_PCI_STOP_SB: U3001.AV25 (~PCISTOPZ); also elsewhere on the board
~SB_PCI_TRDY_SB: U3001.AT25 (~PCITRDYZ); also elsewhere on the board
~SB_RESET: U3001.AR6 (~SYSRSTZ); also elsewhere on the board
~SB_SPI_CS: U3001.AV7 (~SYSCSSPCIS); also elsewhere on the board
~SS2_INT: U3001.E3 (PIO5); also elsewhere on the board
